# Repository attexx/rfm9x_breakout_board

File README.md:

# RFM9x Breakout Board

</br>

### Description

The RFM9x Breakout Board is a breadboard friendly PCB, converting the 2mm pitch connectors on the HopeRF modules to a more user friendly 2.54mm (0.100″) pitch footprint, used in standard breadboards. Using the breadboard, the developers can easily create IoT modules with 430MHz, 868MHz or 905MHz in their projects and add LoRaWAN capabilities to them.

### Features

- small size
- breadboard friendly (pin spacing 2.54mm)
- the board includes combined footprint for SMA edge as well as SMD u.Fl antenna connector, so both connectors can be applied separately or together depends on what is needed
- optional circuit for power indication
- optional pullup resistor to keep high voltage level on NCC pin in case the RFM95W/96W/98W module is connected to MCU that requires programming via FTDI

### Schematic

_schematic_<br />

Nothing special on the schematic. The components R1, R2 and D1 are optional and can be omitted if not needed. R1 is used as pullup to keep high voltage level on the NCC pin. This allows programming the RFM95W/96W/98W module in case the board is interfaced to external microcontroller and ISP is used as a programming interface. R2 and D1 are used as power indication.

### Boards

#### Revision 1b:

Updates in revision 1b include:
- added support for SMD u.Fl antenna connector
- added open source hardware logo to the layout of the board

_top side_<br />

_bottom side_<br />

#### Revision 1:

Initial revision, obsolete.

_top side_<br />

_bottom side_<br />

### BOM

All components are 0805 sized and you can buy them everywhere.

| id | designator | value     | description        | quantity | datasheet             | supplier | note     |
|----|------------|-----------|--------------------|----------|-----------------------|----------|----------|
| 1  | R1         | 10k       | Resistor SMD 0805  | 1        |                       |          | optional |
| 2  | R2         | 330       | Resistor SMD 0805  | 1        |                       |          | optional |
| 3  | C1         | 10uF      | Capacitor SMD 0805 | 1        |                       |          | required |
| 4  | D1         | LED       | LED 0805           | 1        |                       |          | optional |
| 5  | J1         | Connector | SMD Edge Connector | 1        |                       |          | optional |
| 6  | J1         | Connector | SMA u.Fl Connector | 1        |                       |          | optional |
| 7  | U1         | RFM9xW    | RFM9xW module      | 1        | [datasheet][a173d720] | HopeRF   | required |

[a173d720]:https://www.hoperf.com/data/upload/portal/20190801/RFM95W-V2.0.pdf "RFM95x"

### Project status

The most recent version (rev. 1b) is tested and works fine. Previous version (rev. 1) is still valid but obsolete, therefore it is not available for purchase.

### Purchase

The board can be purchased from the [AISLER.net](https://aisler.net/) web store by clicking on this [link](https://aisler.net/p/BNYBJOFL). You can also try to purchase it from 
the [PCBs.io](https://PCBs.io/share/4QJV1) web store, but be aware that recently this site has been inactive, so ordering the board through it may not be successful.

## License

<br />

Copyright © 2019 Boyan Nedkov. All rights reserved.<br />
Licensed under a [Creative Commons Attribution-NonCommercial 4.0 International License][1]. For permissions beyond the scope of this license please [contact me][2] so we can arrange a simple agreement.

[1]: http://creativecommons.org/licenses/by-nc/4.0/
[2]: mailto:attexx@gmx.com

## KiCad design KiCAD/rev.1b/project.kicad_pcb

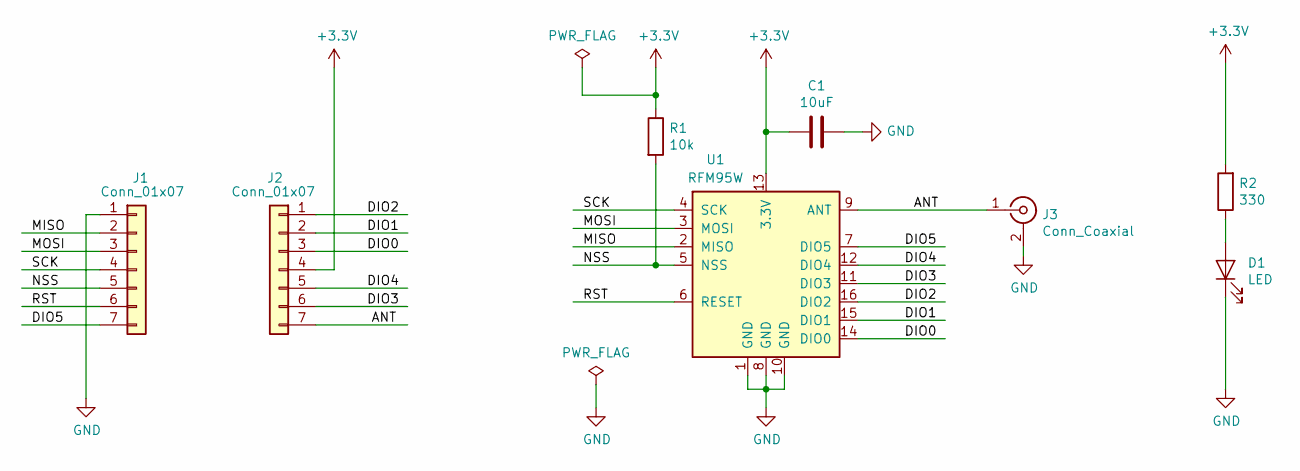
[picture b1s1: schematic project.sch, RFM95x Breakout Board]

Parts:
C1: 10uF; C_0805_2012Metric
D1: LED; LED_0805_2012Metric
J1, J2: Conn_01x07; PinHeader_1x07_P2.54mm_Vertical_2
J3: Conn_Coaxial; Connector_Coaxial_SMA_edge_combined
R1: 10k; R_0805_2012Metric
R2: 330; R_0805_2012Metric
U1: RFM95W

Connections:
+3V3: C1.2, J2.4, R1.1, R2.2, U1.13 (3.3V)
/ANT: J2.7, J3.1 (In), U1.9 (ANT)
/DIO0: J2.3, U1.14 (DIO0)
/DIO1: J2.2, U1.15 (DIO1)
/DIO2: J2.1, U1.16 (DIO2)
/DIO3: J2.6, U1.11 (DIO3)
/DIO4: J2.5, U1.12 (DIO4)
/DIO5: J1.7, U1.7 (DIO5)
/MISO: J1.2, U1.2 (MISO)
/MOSI: J1.3, U1.3 (MOSI)
/NSS: J1.5, R1.2, U1.5 (NSS)
/RST: J1.6, U1.6 (RESET)
/SCK: J1.4, U1.4 (SCK)
GND: C1.1, D1.1 (K), J1.1, J3.2 (Ext), U1.1 (GND), U1.8 (GND), U1.10 (GND)
unnamed: D1.2 (A), R2.1

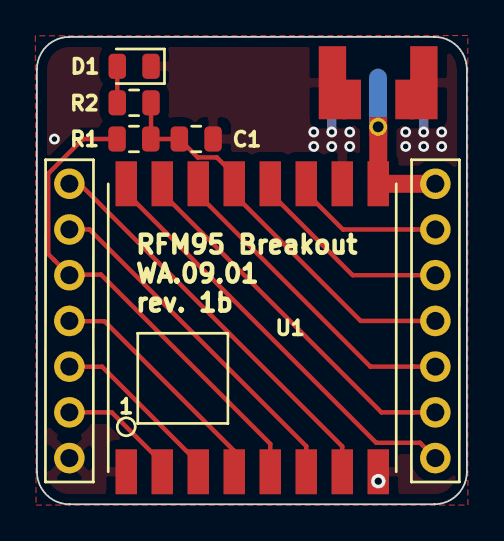
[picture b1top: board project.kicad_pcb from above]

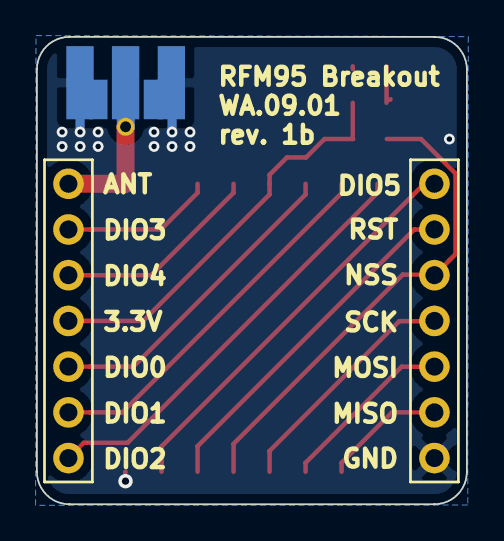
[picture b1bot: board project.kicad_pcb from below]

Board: 2 copper layers, 23.9 x 26.0 mm, 8 parts (3 on the bottom side), 15 nets.

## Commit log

2019-10-28 update description
2019-10-28 update gitignore
2021-03-04 Update README.md
    update
2023-05-16 Update README.md
    added AISLRE web store
2023-05-16 Update README.md
    edited web store information
